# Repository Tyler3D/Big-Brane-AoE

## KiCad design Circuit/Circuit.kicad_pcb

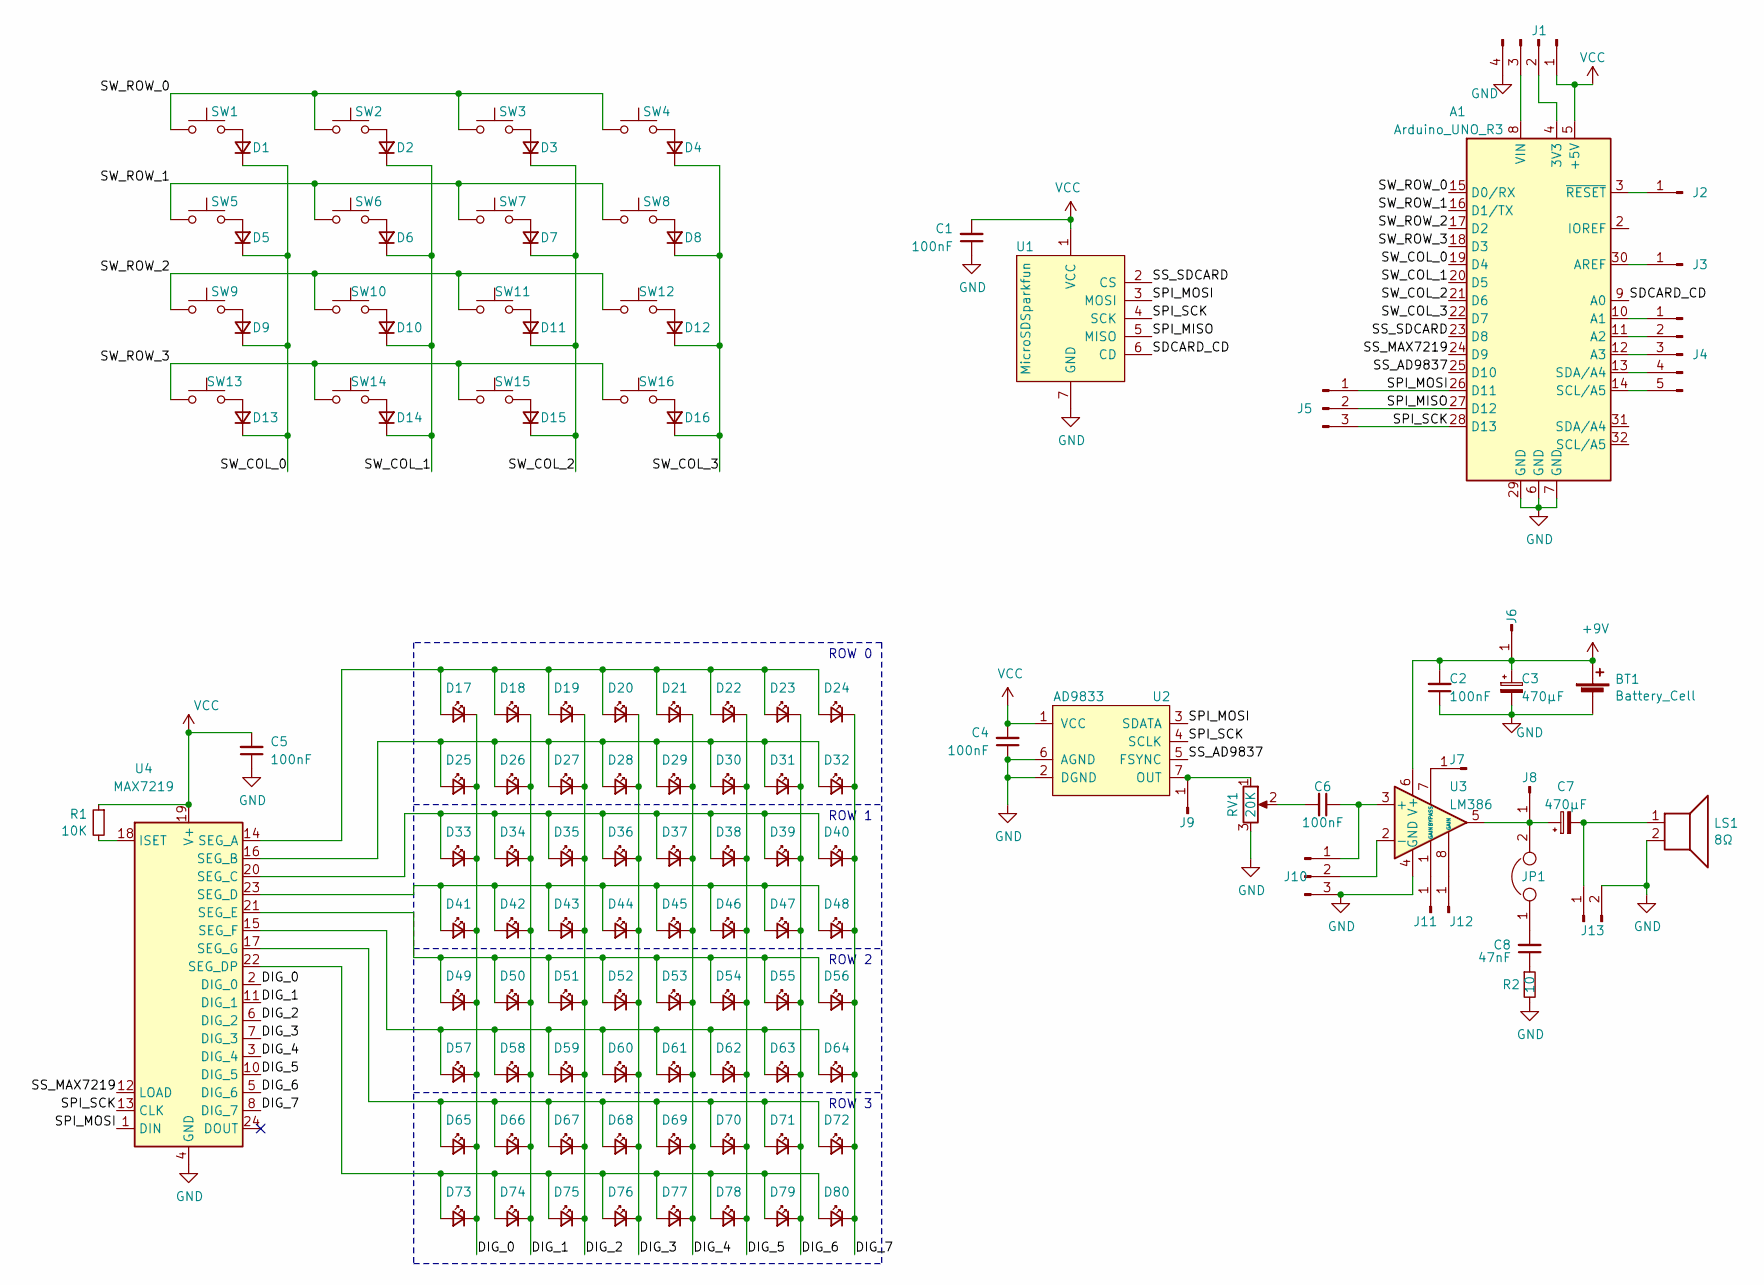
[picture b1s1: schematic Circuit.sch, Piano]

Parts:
A1: Arduino_UNO_R3
BT1: Battery_Cell; JST_EH_B2B-EH-A_1x02_P2.50mm_Vertical
C1, C2, C4, C5, C6: 100nF; C_Disc_D4.3mm_W1.9mm_P5.00mm
C3, C7: 470μF; CP_Radial_D14.0mm_P7.50mm
C8: 47nF; C_Disc_D4.3mm_W1.9mm_P5.00mm
D1, D2, D3, D4, D5, D6, D7, D8, D9, D10, D11, D12, D13, D14, D15, D16: D_Small; D_SMB_Handsoldering
D17, D18, D19, D20, D21, D22, D23, D24, D25, D26, D27, D28, D29, D30, D31, D32, D33, D34, D35, D36, D37, D38, D39, D40, D41, D42, D43, D44, D45, D46, D47, D48, D49, D50, D51, D52, D53, D54, D55, D56, D57, D58, D59, D60, D61, D62, D63, D64, D65, D66, D67, D68, D69, D70, D71, D72, D73, D74, D75, D76, D77, D78, D79, D80: LED_Small; LED_D3.0mm_FlatTop
J1: POWER; PinHeader_1x04_P2.54mm_Vertical
J2: RESET; PinHeader_1x01_P2.54mm_Vertical
J3: AREF; PinHeader_1x01_P2.54mm_Vertical
J4: Analog Breakout; PinHeader_1x05_P2.54mm_Vertical
J5: SPI (MOSI, MISO, SCK); PinHeader_1x03_P2.54mm_Vertical
J6: LM386 VCC; PinHeader_1x01_P2.54mm_Vertical
J7: BYPASS; PinHeader_1x01_P2.54mm_Vertical
J8: LM386 OUT; PinHeader_1x01_P2.54mm_Vertical
J9: AD9833 OUT; PinHeader_1x01_P2.54mm_Vertical
J10: LM386 IN; PinHeader_1x03_P2.54mm_Vertical
J11: GAIN 1; PinHeader_1x01_P2.54mm_Vertical
J12: GAIN 8; PinHeader_1x01_P2.54mm_Vertical
J13: SPKR; PinHeader_1x02_P2.54mm_Vertical
JP1: Jumper; PinHeader_1x02_P2.54mm_Vertical
LS1: 8Ω; JST_EH_B2B-EH-A_1x02_P2.50mm_Vertical
R1: 10K; R_Axial_DIN0207_L6.3mm_D2.5mm_P7.62mm_Horizontal
R2: 10; R_Axial_DIN0207_L6.3mm_D2.5mm_P7.62mm_Horizontal
RV1: 20K; Potentiometer_Vishay_148-149_Single_Horizontal
SW1, SW2, SW3, SW4, SW5, SW6, SW7, SW8, SW9, SW10, SW11, SW12, SW13, SW14, SW15, SW16: SW_Push; SW_Cherry_MX_1.00u_PCB
U1: MicroSDSparkfun; PinHeader_1x07_P2.54mm_Horizontal
U2: AD9833; PinHeader_1x07_P2.54mm_Vertical
U3: LM386; DIP-8_W7.62mm_Socket_LongPads
U4: MAX7219; DIP-24_W7.62mm_LongPads

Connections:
+9V: BT1.1 (+), C2.2, C3.1, J6.1, U3.6 (V+)
/DIG_0: D17.1 (K), D25.1 (K), D33.1 (K), D41.1 (K), D49.1 (K), D57.1 (K), D65.1 (K), D73.1 (K), U4.2 (DIG_0)
/DIG_1: D18.1 (K), D26.1 (K), D34.1 (K), D42.1 (K), D50.1 (K), D58.1 (K), D66.1 (K), D74.1 (K), U4.11 (DIG_1)
/DIG_2: D19.1 (K), D27.1 (K), D35.1 (K), D43.1 (K), D51.1 (K), D59.1 (K), D67.1 (K), D75.1 (K), U4.6 (DIG_2)
/DIG_3: D20.1 (K), D28.1 (K), D36.1 (K), D44.1 (K), D52.1 (K), D60.1 (K), D68.1 (K), D76.1 (K), U4.7 (DIG_3)
/DIG_4: D21.1 (K), D29.1 (K), D37.1 (K), D45.1 (K), D53.1 (K), D61.1 (K), D69.1 (K), D77.1 (K), U4.3 (DIG_4)
/DIG_5: D22.1 (K), D30.1 (K), D38.1 (K), D46.1 (K), D54.1 (K), D62.1 (K), D70.1 (K), D78.1 (K), U4.10 (DIG_5)
/DIG_6: D23.1 (K), D31.1 (K), D39.1 (K), D47.1 (K), D55.1 (K), D63.1 (K), D71.1 (K), D79.1 (K), U4.5 (DIG_6)
/DIG_7: D24.1 (K), D32.1 (K), D40.1 (K), D48.1 (K), D56.1 (K), D64.1 (K), D72.1 (K), D80.1 (K), U4.8 (DIG_7)
/SDCARD_CD: A1.9 (A0), U1.6 (CD)
/SPI_MISO: A1.27 (D12), J5.2, U1.5 (MISO)
/SPI_MOSI: A1.26 (D11), J5.1, U1.3 (MOSI), U2.3 (SDATA), U4.1 (DIN)
/SPI_SCK: A1.28 (D13), J5.3, U1.4 (SCK), U2.4 (SCLK), U4.13 (CLK)
/SS_AD9837: A1.25 (D10), U2.5 (FSYNC)
/SS_MAX7219: A1.24 (D9), U4.12 (LOAD)
/SS_SDCARD: A1.23 (D8), U1.2 (CS)
/SW_COL_0: A1.19 (D4), D1.1 (K), D5.1 (K), D9.1 (K), D13.1 (K)
/SW_COL_1: A1.20 (D5), D2.1 (K), D6.1 (K), D10.1 (K), D14.1 (K)
/SW_COL_2: A1.21 (D6), D3.1 (K), D7.1 (K), D11.1 (K), D15.1 (K)
/SW_COL_3: A1.22 (D7), D4.1 (K), D8.1 (K), D12.1 (K), D16.1 (K)
/SW_ROW_0: A1.15 (D0/RX), SW1.2, SW2.2, SW3.2, SW4.2
/SW_ROW_1: A1.16 (D1/TX), SW5.2, SW6.2, SW7.2, SW8.2
/SW_ROW_2: A1.17 (D2), SW9.2, SW10.2, SW11.2, SW12.2
/SW_ROW_3: A1.18 (D3), SW13.2, SW14.2, SW15.2, SW16.2
GND: A1.6 (GND), A1.7 (GND), A1.29 (GND), BT1.2 (-), C1.1, C2.1, C3.2, C4.1, C5.1, J1.4, J10.3, J13.2, LS1.2, R2.2, RV1.3, U1.7 (GND), U2.2 (DGND), U2.6 (AGND), U3.4 (GND), U4.4 (GND), U4.9 (GND)
unnamed: A1.3 (~RESET), J2.1
unnamed: A1.4 (3V3), J1.2
unnamed: A1.8 (VIN), J1.3
unnamed: A1.10 (A1), J4.1
unnamed: A1.11 (A2), J4.2
unnamed: A1.12 (A3), J4.3
unnamed: A1.13 (SDA/A4), J4.4
unnamed: A1.14 (SCL/A5), J4.5
unnamed: A1.30 (AREF), J3.1
unnamed: C6.1, J10.1, U3.3 (+)
unnamed: C6.2, RV1.2
unnamed: C7.1, J8.1, JP1.2, U3.5
unnamed: C7.2, J13.1, LS1.1
unnamed: C8.1, R2.1
unnamed: C8.2, JP1.1
unnamed: D1.2 (A), SW1.1
unnamed: D2.2 (A), SW2.1
unnamed: D3.2 (A), SW3.1
unnamed: D4.2 (A), SW4.1
unnamed: D5.2 (A), SW5.1
unnamed: D6.2 (A), SW6.1
unnamed: D7.2 (A), SW7.1
unnamed: D8.2 (A), SW8.1
unnamed: D9.2 (A), SW9.1
unnamed: D10.2 (A), SW10.1
unnamed: D11.2 (A), SW11.1
unnamed: D12.2 (A), SW12.1
unnamed: D13.2 (A), SW13.1
unnamed: D14.2 (A), SW14.1
unnamed: D15.2 (A), SW15.1
unnamed: D16.2 (A), SW16.1
unnamed: D17.2 (A), D18.2 (A), D19.2 (A), D20.2 (A), D21.2 (A), D22.2 (A), D23.2 (A), D24.2 (A), U4.14 (SEG_A)
unnamed: D25.2 (A), D26.2 (A), D27.2 (A), D28.2 (A), D29.2 (A), D30.2 (A), D31.2 (A), D32.2 (A), U4.16 (SEG_B)
unnamed: D33.2 (A), D34.2 (A), D35.2 (A), D36.2 (A), D37.2 (A), D38.2 (A), D39.2 (A), D40.2 (A), U4.20 (SEG_C)
unnamed: D41.2 (A), D42.2 (A), D43.2 (A), D44.2 (A), D45.2 (A), D46.2 (A), D47.2 (A), D48.2 (A), U4.23 (SEG_D)
unnamed: D49.2 (A), D50.2 (A), D51.2 (A), D52.2 (A), D53.2 (A), D54.2 (A), D55.2 (A), D56.2 (A), U4.21 (SEG_E)
unnamed: D57.2 (A), D58.2 (A), D59.2 (A), D60.2 (A), D61.2 (A), D62.2 (A), D63.2 (A), D64.2 (A), U4.15 (SEG_F)
unnamed: D65.2 (A), D66.2 (A), D67.2 (A), D68.2 (A), D69.2 (A), D70.2 (A), D71.2 (A), D72.2 (A), U4.17 (SEG_G)
unnamed: D73.2 (A), D74.2 (A), D75.2 (A), D76.2 (A), D77.2 (A), D78.2 (A), D79.2 (A), D80.2 (A), U4.22 (SEG_DP)
unnamed: J7.1, U3.7 (BYPASS)
unnamed: J9.1, RV1.1, U2.7 (OUT)
unnamed: J10.2, U3.2 (-)
unnamed: J11.1, U3.1 (GAIN)
unnamed: J12.1, U3.8 (GAIN)
unnamed: R1.2, U4.18 (ISET)
VCC: A1.5 (+5V), C1.2, C4.2, C5.2, J1.1, R1.1, U1.1 (VCC), U2.1 (VCC), U4.19 (V+)

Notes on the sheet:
ROW 0
ROW 1
ROW 2
ROW 3

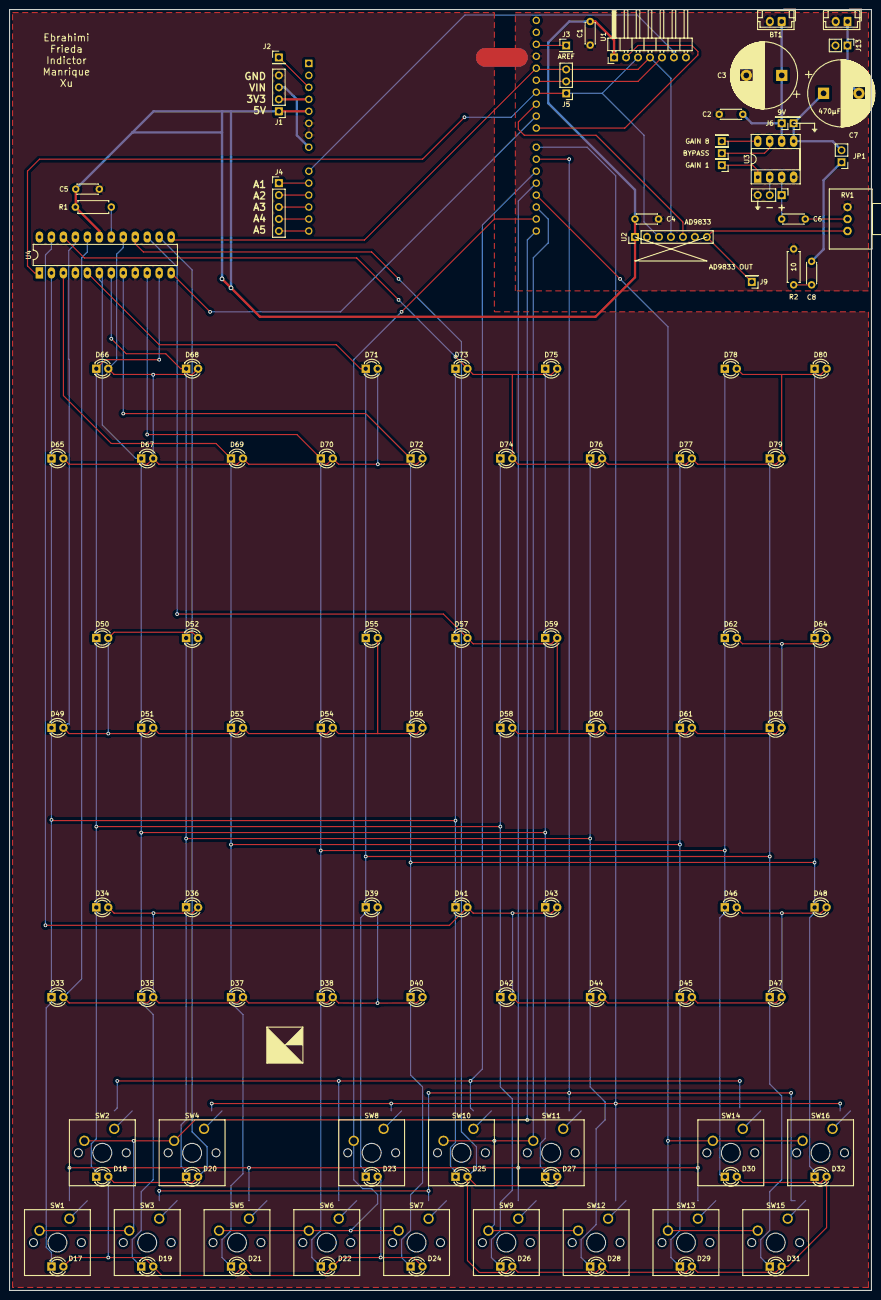
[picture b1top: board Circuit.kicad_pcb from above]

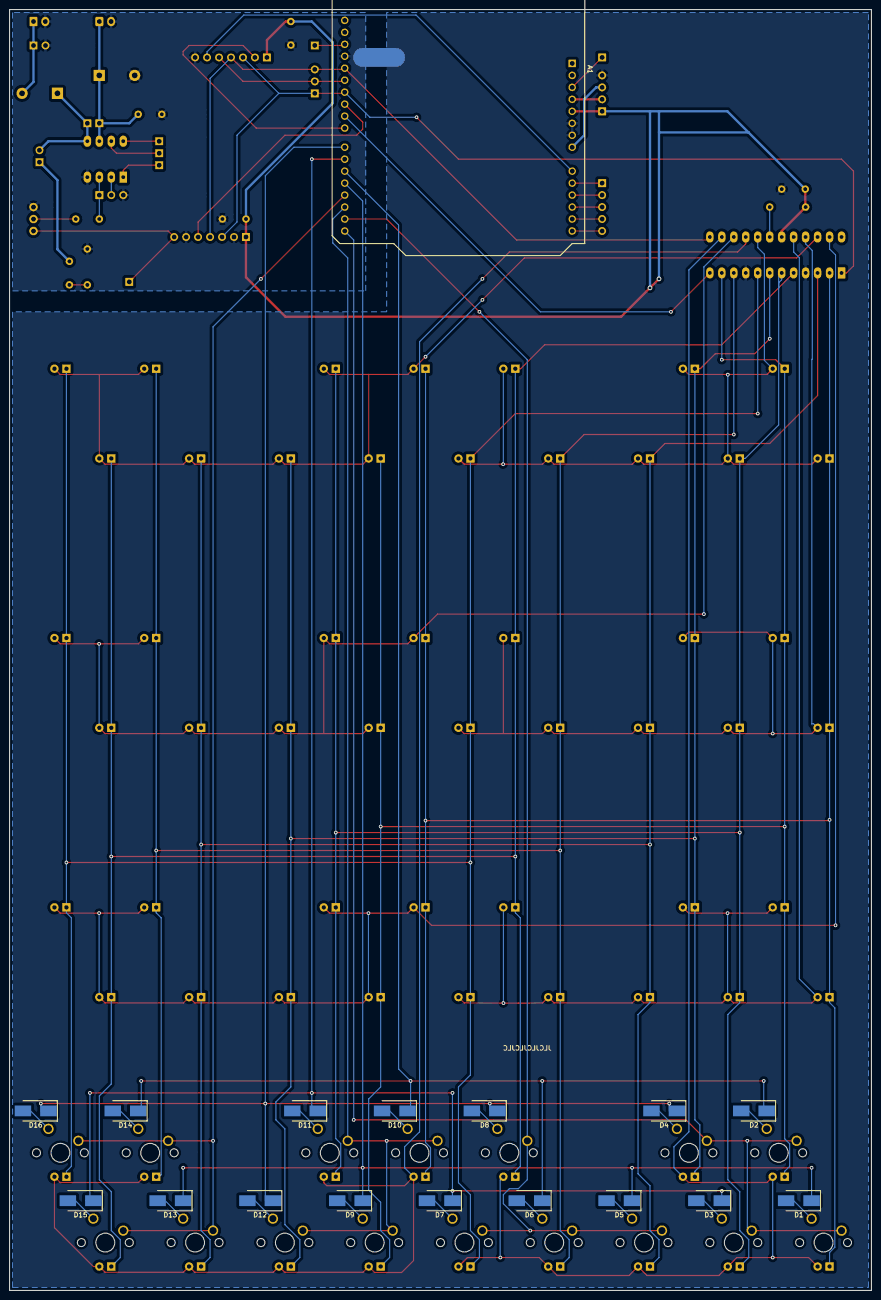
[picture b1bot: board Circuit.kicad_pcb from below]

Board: 2 copper layers, 182.9 x 271.8 mm, 128 parts (17 on the bottom side), 71 nets.

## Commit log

2020-11-10 Started circuit schematic design. Finished button and LED Matrices.
2020-11-14 Add tones
2020-11-26 Make progress with audio and start laying out PCB.
2020-12-03 Added more traces, added all footprints, and made minor corrections to schematic.
2020-12-03 Fixed tones.
2020-12-09 Adding schematic for all to see.
2020-12-13 Added button, LED, and audio code.
2020-12-13 Add Gerbers.
2020-12-13 Upload final version of Schematic and board layout.
2020-12-14 Basic functionality completed
    Each song is ended with three 0's and an 0xff to signify a song's end. Since std::cin picks the first char available, this currently only works with 10 keys (0-9). But with a revamped buttons class, 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
2020-12-14 Made Adjustments so it can compile on Arduino.
    Needs testing to see if anything broke
2020-12-14 Fixes some mistakes
2020-12-20 Final touches on circuit.
2020-12-20 Added all code necessary to create functioning demo.
2020-12-25 General improvements in the code
    It has a timer that gives a player a set amount of time to respond
2020-12-25 Forgot to get rid of these
